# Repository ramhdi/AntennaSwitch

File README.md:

# AntennaSwitch

Antenna Switch - a project of Telemetry Departement, Aksantara ITB

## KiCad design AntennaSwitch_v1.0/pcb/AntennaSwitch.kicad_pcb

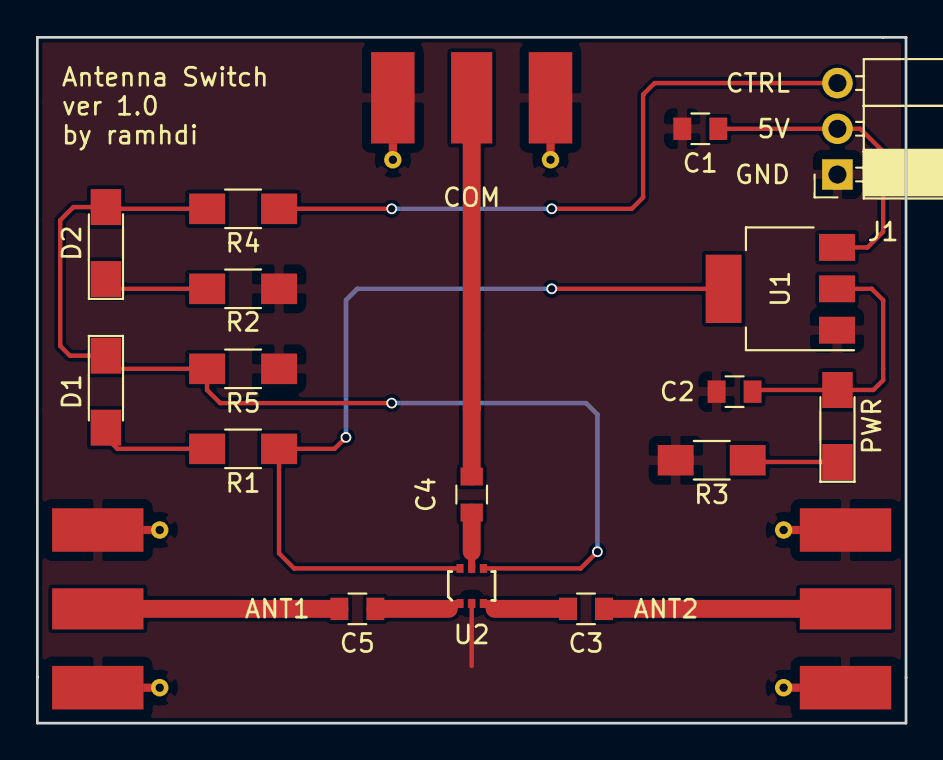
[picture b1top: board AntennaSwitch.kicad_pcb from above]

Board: 2 copper layers, 48.3 x 38.1 mm, 19 parts (0 on the bottom side), 14 nets.

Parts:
ANT1: ANT_1; Molex_SMA_Jack_Edge_Mount
ANT2: ANT_2; Molex_SMA_Jack_Edge_Mount
C1, C2, C3, C4, C5: 10u; C_0805
COM: ANT_C; Molex_SMA_Jack_Edge_Mount
D1, D2: LED; LED_1206_HandSoldering
J1: INPUT; Socket_Strip_Angled_1x03_Pitch2.54mm
PWR: LED; LED_1206_HandSoldering
R1, R2: 400; R_1206_HandSoldering
R3: 1k; R_1206_HandSoldering
R4: 100; R_1206_HandSoldering
R5: 200; R_1206_HandSoldering
U1: AP1117-33; SOT-223-3_TabPin2
U2: PE4259

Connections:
+3V3: C2.1, PWR.2, R1.2, U1.2, U2.6
+5V: C1.1, J1.2, U1.3
ANT_1: C5.2, U2.1
ANT_2: C3.2, U2.3
ANT_C: C4.2, U2.5
CTRL: J1.3, R4.2
GND: ANT1.2, ANT2.2, C1.2, C2.2, COM.2, J1.1, R2.1, R3.2, R5.2, U1.1, U2.2
unnamed: ANT2.1, C3.1
unnamed: C4.1, COM.1
unnamed: ANT1.1, C5.1
unnamed: D1.1, D2.2, R4.1, R5.1, U2.4
unnamed: D1.2, R1.1
unnamed: D2.1, R2.2
unnamed: PWR.1, R3.1

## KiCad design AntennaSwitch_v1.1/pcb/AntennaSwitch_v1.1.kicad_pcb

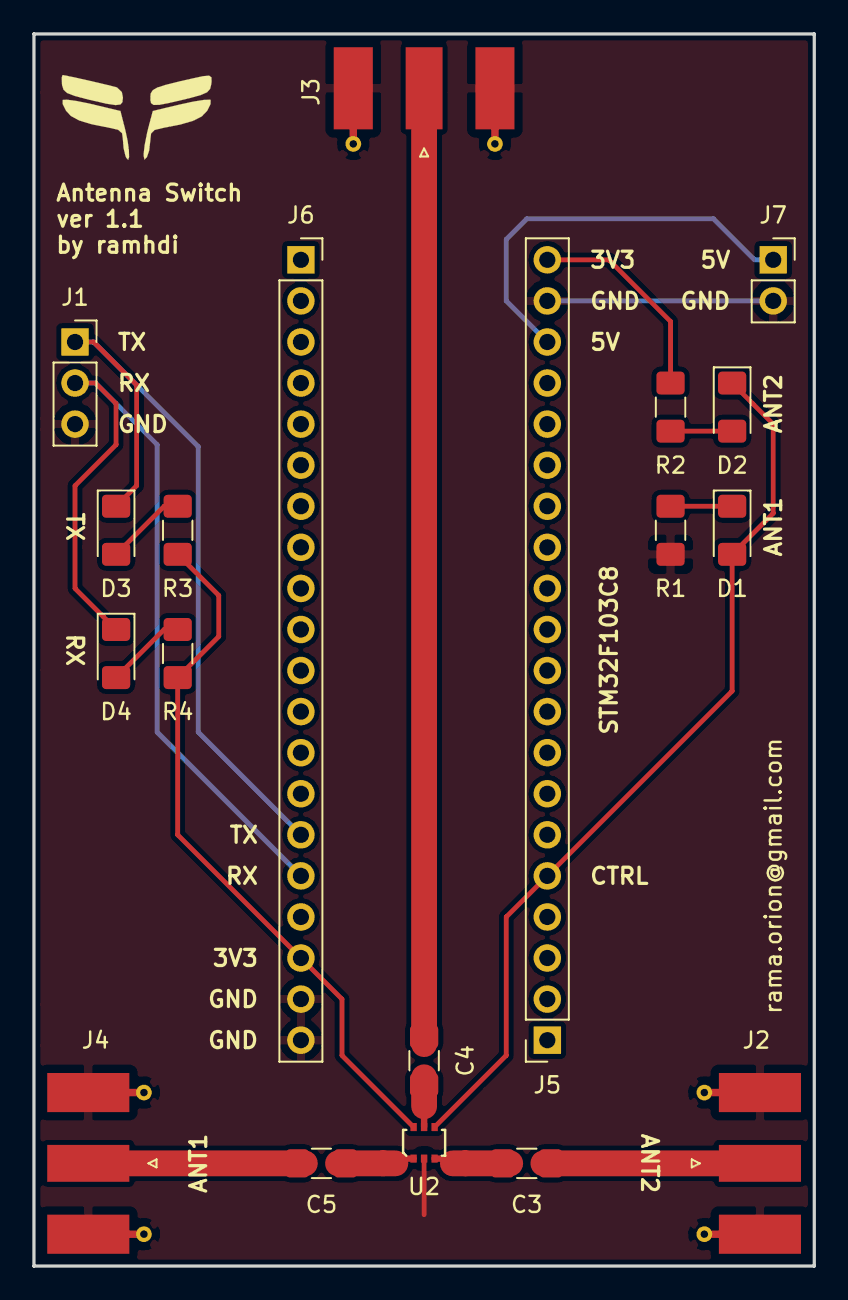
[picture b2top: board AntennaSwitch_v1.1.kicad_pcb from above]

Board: 2 copper layers, 48.3 x 76.2 mm, 19 parts (0 on the bottom side), 16 nets.

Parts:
C3, C4, C5: 10u; C_1206_3216Metric_Pad1.42x1.75mm_HandSolder
D1, D2, D3, D4: LED; LED_1206_3216Metric_Pad1.42x1.75mm_HandSolder
J1: Conn_01x03; PinSocket_1x03_P2.54mm_Vertical
J2, J3, J4: Conn_Coaxial; SMA_Molex_73251-1153_EdgeMount_Horizontal
J5: STM32_L; PinSocket_1x20_P2.54mm_Vertical
J6: STM32_R; PinSocket_1x20_P2.54mm_Vertical
J7: Conn_01x02; PinSocket_1x02_P2.54mm_Vertical
R1, R2, R3, R4: 220; R_1206_3216Metric_Pad1.42x1.75mm_HandSolder
U2: PE4259

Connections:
+3V3: J5.20, J6.18, R2.2, R3.1, R4.1, U2.6
+5V: J5.18, J7.1
ANT_1: C5.2, U2.1
ANT_2: C3.2, U2.3
ANT_C: C4.2, U2.5
CTRL: D1.2, D2.1, J5.5, U2.4
GND: J1.3, J2.2, J3.2, J4.2, J5.19, J6.19, J6.20, J7.2, R1.1, U2.2
unnamed: C3.1, J2.1
unnamed: C4.1, J3.1
unnamed: C5.1, J4.1
unnamed: D1.1, R1.2
unnamed: D2.2, R2.1
unnamed: D3.2, R3.2
unnamed: D4.2, R4.2
RX: D4.1, J1.2, J6.16
TX: D3.1, J1.1, J6.15

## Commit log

2018-12-06 Upload New File
2018-12-06 Add new directory
2018-12-07 Added earlier version (v1.0)
2019-02-23 Updated MAVlink library
2019-02-23 Added request home position and send heartbeat procedure
2019-02-25 Deleted PCB files
